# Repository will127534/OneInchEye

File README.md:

# OneInchEye: OpenSource IMX283 Camera Board for Raspberry Pi

### Update on 2024/03/24
This project is also compatiable with RPI5, the quickstart guide has been updated.  

## Introduction
Welcome to the **OneInchEye** project, an open-source camera board designed for Raspberry Pi Compute Module 4 boards using the IMX283 one-inch sensor. This project aims to provide a high-quality, affordable, and accessible camera module for advanced Raspberry Pi projects. The board is designed using KiCad v6, a popular open-source electronics design automation (EDA) software.

OneInchEye captures stunning high-resolution images and videos with improved low-light performance and dynamic range. It's perfect for photography enthusiasts, developers, and makers who want to level up their Raspberry Pi projects with a powerful camera. The board also features a TMP117 temperature sensor for accurate temperature readings.

**Please note that the OneInchEye is not compatible with most Raspberry Pi boards because it requires 22-pin FPC connector with 4-lane MIPI-CSI interface. Ensure compatibility with your specific board before proceeding.**

## Features
* 1-inch IMX283 sensor
* **Open-source hardware and software**
* Integrated TMP117 temperature sensor
* Integrated 6-axis IMU ICM42688-P
* Compatible with Raspberry Pi Compute Module 4 boards with a 22-pin FPC connector and 4-lane MIPI-CSI (same pinout as Raspberry Pi Compute Module 4 IO Board)

## Support
For questions, issues, or suggestions, please open an issue in the [GitHub repository](https://github.com/will127534/OneInchEye/issues)  
Also see [Quick Start Guide](https://github.com/will127534/OneInchEye/wiki/OneInchEye-Quick-Start-Guide)

## MISC stuff  
1. Blog post(?) here: https://will127534.github.io/OneInchEye/
1. I know the decoupling capacitors in sch are a mess.....  
2. IMU is hook up at the 1.8V LDO, but that LDO is controlled by CAM_GPIO (or think as a enable pin for the camera module), so it will function only when the camera is active.
3. IMU's FSYNC is conencted to VSYNC output from the sensor for measurements/frame alignment 
4. Temperature sensor is connected to 3.3V FPC input
5. There is no clock sync function for the CMOS sensor, so the XVS and XHS are output only.  
6. QWIIC is mainly for hooking up to other I2C devices so you don't have to connect yet another cable if you add additional I2C sensor to the board. But it also serves as I2C debug port to hook up external logic analyzer.  
7. This board is actually quite easy to assemble, if you want to build board yourself, you can use JLCPCB to do the PCBA on component side and do the CMOS side with low temperature soldering paste yourself if you can source the CMOS sensor. The JLCPCB BOM and Position list is also provided.
8. Limited quantity on Tindle: https://www.tindie.com/products/will123321/oneincheye/

## License
This project is released under the MIT License.

Thanks to ChatGPT helping me generating most of the Readme, see if you can spot which section I typed.

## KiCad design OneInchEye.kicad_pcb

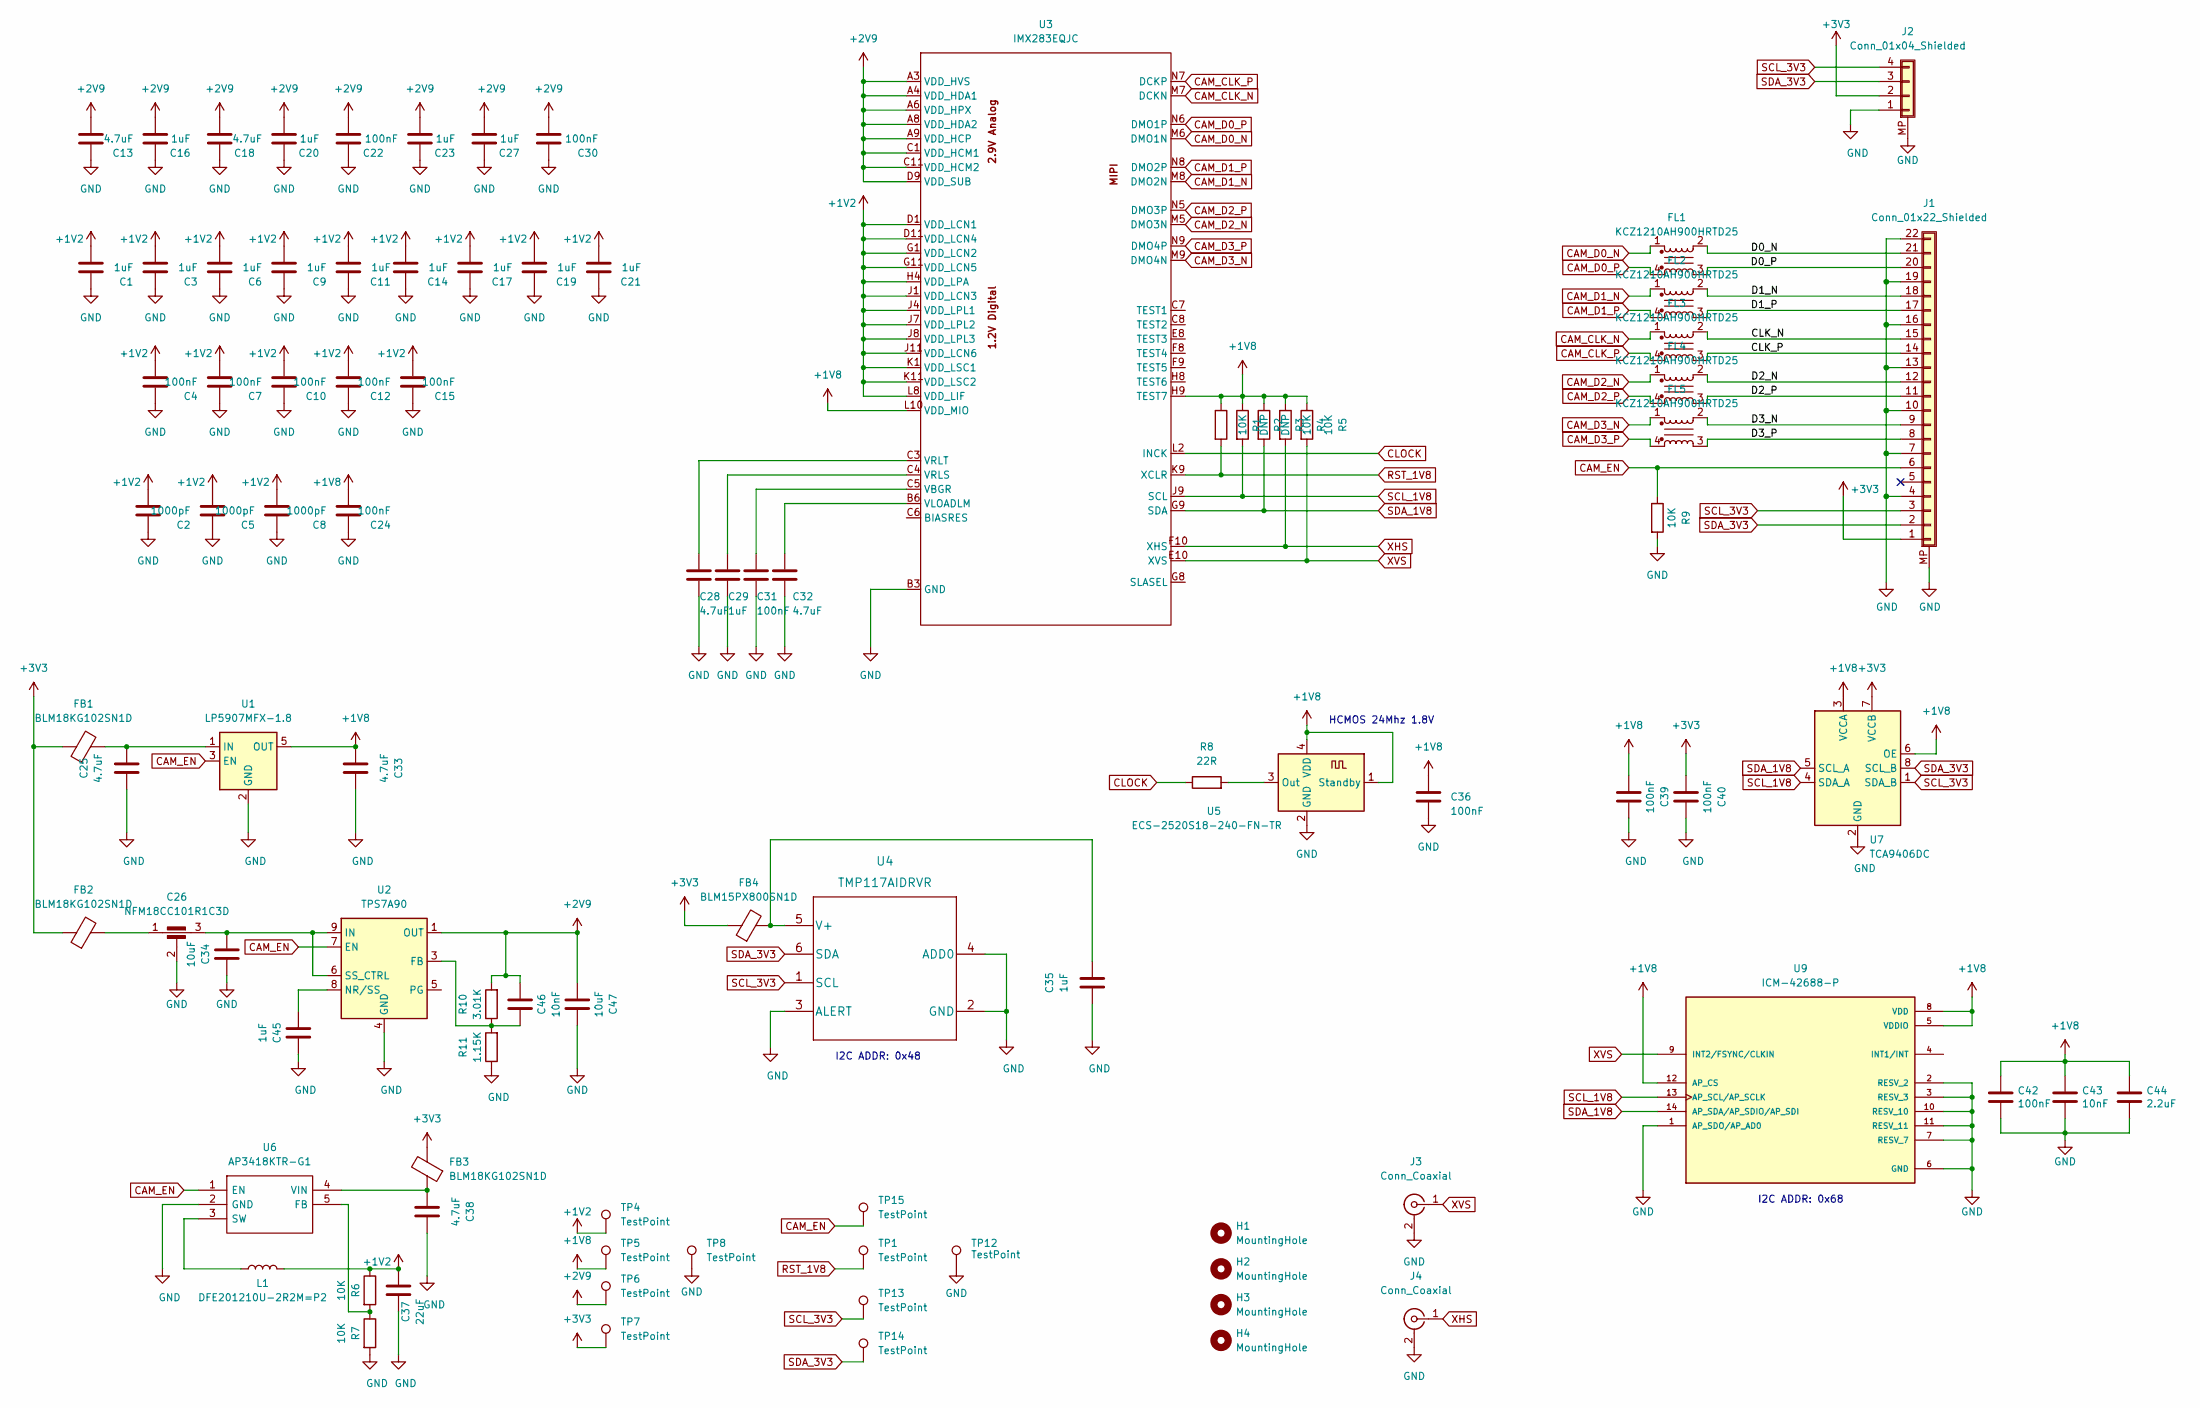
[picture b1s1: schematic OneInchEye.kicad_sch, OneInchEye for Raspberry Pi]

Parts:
C1, C3, C6, C9, C11, C14, C16, C17, C19, C20, C21, C23, C27, C29, C35, C45: 1uF; C_0402_1005Metric
C2, C5, C8: 1000pF; C_0402_1005Metric
C4, C7, C10, C12, C15, C22, C24, C30, C31, C36, C39, C40, C42: 100nF; C_0402_1005Metric
C13, C18, C25, C28, C32, C33, C38: 4.7uF; C_0603_1608Metric
C26: NFM18CC101R1C3D
C34, C47: 10uF; C_0603_1608Metric
C37: 22uF; C_0603_1608Metric
C43, C46: 10nF; C_0402_1005Metric
C44: 2.2uF; C_0402_1005Metric
FB1, FB2, FB3: BLM18KG102SN1D; L_0603_1608Metric
FB4: BLM15PX800SN1D; L_0402_1005Metric
FL1, FL2, FL3, FL4, FL5: KCZ1210AH900HRTD25; DLP11SA350HL2B
H1, H2, H3, H4: MountingHole; MountingHole_2.2mm_M2
J1: Conn_01x22_Shielded; TF3822S05SV830
J2: Conn_01x04_Shielded; JST_SH_BM04B-SRSS-TB_1x04-1MP_P1.00mm_Vertical
J3, J4: Conn_Coaxial; U.FL_Hirose_U.FL-R-SMT-1_Vertical
L1: DFE201210U-2R2M=P2; L_0805_2012Metric
R1, R4, R5, R6, R7, R9: 10K; R_0402_1005Metric
R2, R3: DNP; R_0402_1005Metric
R8: 22R; R_0402_1005Metric
R10: 3.01K; R_0402_1005Metric
R11: 1.15K; R_0402_1005Metric
TP1, TP4, TP5, TP6, TP7, TP8, TP12, TP13, TP14, TP15: TestPoint; TestPoint_Pad_D1.0mm
U1: LP5907MFX-1.8; SOT-23-5
U2: TPS7A90; Texas_S-PDSO-N10_EP1.2x2mm
U3: IMX283EQJC; IMX283
U4: TMP117AIDRVR
U5: ECS-2520S18-240-FN-TR; Oscillator_SMD_Abracon_ASDMB-4Pin_2.5x2.0mm
U6: AP3418KTR-G1; SOT-23-5; Mouser Part Number 621-AP3418KTR-G1
U7: TCA9406DC; TCA9406DCUR
U9: ICM-42688-P; IIM42352; PARTREV 1.2

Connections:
+1V2: C1.2, C2.2, C3.2, C4.2, C5.2, C6.2, C7.2, C8.2, C9.2, C10.2, C11.2, C12.2, C14.2, C15.2, C17.2, C19.2, C21.2, C37.2, L1.2, R6.1, TP4.1, U3.D1 (VDD_LCN1), U3.D11 (VDD_LCN4), U3.G1 (VDD_LCN2), U3.G11 (VDD_LCN5), U3.H4 (VDD_LPA), U3.J1 (VDD_LCN3), U3.J4 (VDD_LPL1), U3.J7 (VDD_LPL2), U3.J8 (VDD_LPL3), U3.J11 (VDD_LCN6), U3.K1 (VDD_LSC1), U3.K11 (VDD_LSC2), U3.L8 (VDD_LIF)
+1V8: C24.2, C33.1, C36.1, C39.1, C42.1, C43.1, C44.1, R1.1, R2.1, R3.1, R4.1, R5.1, TP5.1, U1.5 (OUT), U3.H9 (TEST7), U3.L10 (VDD_MIO), U5.1 (Standby), U5.4 (VDD), U7.3 (VCCA), U7.6 (OE), U9.5 (VDDIO), U9.8 (VDD), U9.12 (AP_CS)
+2V9: C13.2, C16.2, C18.2, C20.2, C22.2, C23.2, C27.2, C30.2, C46.2, C47.1, R10.2, TP6.1, U2.1 (OUT), U2.2 (OUT), U3.A3 (VDD_HVS), U3.A4 (VDD_HDA1), U3.A6 (VDD_HPX), U3.A8 (VDD_HDA2), U3.A9 (VDD_HCP), U3.C1 (VDD_HCM1), U3.C11 (VDD_HCM2), U3.D9 (VDD_SUB)
+3V3: C40.1, FB1.1, FB2.1, FB3.2, FB4.1, J1.1, J2.2, TP7.1, U7.7 (VCCB)
/CLK_N: FL3.2, J1.15
/CLK_P: FL3.3, J1.14
/D0_N: FL1.2, J1.21
/D0_P: FL1.3, J1.20
/D1_N: FL2.2, J1.18
/D1_P: FL2.3, J1.17
/D2_N: FL4.2, J1.12
/D2_P: FL4.3, J1.11
/D3_N: FL5.2, J1.9
/D3_P: FL5.3, J1.8
CAM_CLK_N: FL3.1, U3.M7 (DCKN)
CAM_CLK_P: FL3.4, U3.N7 (DCKP)
CAM_D0_N: FL1.1, U3.M6 (DMO1N)
CAM_D0_P: FL1.4, U3.N6 (DMO1P)
CAM_D1_N: FL2.1, U3.M8 (DMO2N)
CAM_D1_P: FL2.4, U3.N8 (DMO2P)
CAM_D2_N: FL4.1, U3.M5 (DMO3N)
CAM_D2_P: FL4.4, U3.N5 (DMO3P)
CAM_D3_N: FL5.1, U3.M9 (DMO4N)
CAM_D3_P: FL5.4, U3.N9 (DMO4P)
CAM_EN: J1.6, R9.1, TP15.1, U1.3 (EN), U2.7 (EN), U6.1 (EN)
CLOCK: R8.1, U3.L2 (INCK)
GND: C1.1, C2.1, C3.1, C4.1, C5.1, C6.1, C7.1, C8.1, C9.1, C10.1, C11.1, C12.1, C13.1, C14.1, C15.1, C16.1, C17.1, C18.1, C19.1, C20.1, C21.1, C22.1, C23.1, C24.1, C25.1, C26.2, C27.1, C28.2, C29.2, C30.1, C31.2, C32.2, C33.2, C34.2, C35.1, C36.2, C37.1, C38.2, C39.2, C40.2, C42.2, C43.2, C44.2, C45.2, C47.2, J1.4, J1.7, J1.10, J1.13, J1.16, J1.19, J1.22, J1.MP (Shield), J2.1, J2.MP (Shield), J3.2 (Ext), J4.2 (Ext), R7.2, R9.2, R11.1, TP8.1, TP12.1, U1.2 (GND), U2.4 (GND), U2.11 (GND), U3.B3 (GND), U3.B4 (GND2), U3.B5 (GND3), U3.B7 (GND4), U3.B8 (GND5), U3.B9 (GND6), U3.C2 (GND8), U3.C10 (GND7), U3.D2 (GND9), U3.D10 (GND10), U3.G2 (GND11), U3.G10 (GND12), U3.H2 (GND13), U3.H3 (GND14), U3.H10 (GND15), U3.J2 (GND16), U3.J10 (GND17), U3.K2 (GND18), U3.K4 (GND19), U3.K7 (GND20), U3.K8 (GND21), U3.K10 (GND22), U3.L7 (GND23), U3.L9 (GND24), U3.N4 (GND25), U4.2 (GND), U4.3 (ALERT), U4.4 (ADD0), U5.2 (GND), U6.2 (GND), U7.2 (GND), U9.1 (AP_SDO/AP_AD0), U9.2 (RESV_2), U9.3 (RESV_3), U9.6 (GND), U9.7 (RESV_7), U9.10 (RESV_10), U9.11 (RESV_11)
unnamed: C26.1, FB2.2
unnamed: C25.2, FB1.2, U1.1 (IN)
unnamed: C46.1, R10.1, R11.2, U2.3 (FB)
unnamed: C45.1, U2.8 (NR/SS)
unnamed: C26.3, C34.1, U2.6 (SS_CTRL), U2.9 (IN), U2.10 (IN)
unnamed: C31.1, U3.C5 (VBGR)
unnamed: C32.1, U3.B6 (VLOADLM)
unnamed: C29.1, U3.C4 (VRLS)
unnamed: C28.1, U3.C3 (VRLT)
unnamed: C35.2, FB4.2, U4.5 (V+)
unnamed: R8.2, U5.3 (Out)
unnamed: R6.2, R7.1, U6.5 (FB)
unnamed: L1.1, U6.3 (SW)
unnamed: C38.1, FB3.1, U6.4 (VIN)
RST_1V8: R1.2, TP1.1, U3.K9 (XCLR)
SCL_1V8: R2.2, U3.J9 (SCL), U7.4 (SDA_A), U9.13 (AP_SCL/AP_SCLK)
SCL_3V3: J1.3, J2.4, TP13.1, U4.1 (SCL), U7.1 (SDA_B)
SDA_1V8: R3.2, U3.G9 (SDA), U7.5 (SCL_A), U9.14 (AP_SDA/AP_SDIO/AP_SDI)
SDA_3V3: J1.2, J2.3, TP14.1, U4.6 (SDA), U7.8 (SCL_B)
XHS: J4.1 (In), R4.2, U3.F10 (XHS)
XVS: J3.1 (In), R5.2, U3.E10 (XVS), U9.9 (INT2/FSYNC/CLKIN)

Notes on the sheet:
I2C ADDR: 0x48
I2C ADDR: 0x68
HCMOS 24Mhz 1.8V

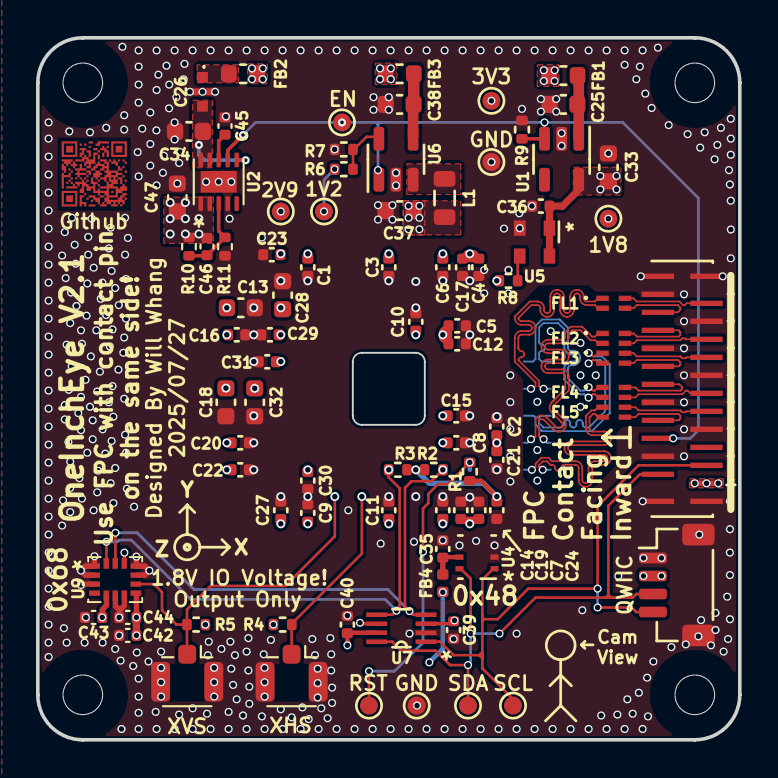
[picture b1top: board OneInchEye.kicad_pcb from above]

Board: 4 copper layers, 39.0 x 39.0 mm, 93 parts (1 on the bottom side), 48 nets.

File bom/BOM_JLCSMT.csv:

Comment,Designator,Footprint,JLCPCB Part #（optional）
100nF,"C7,C36,C22,C15,C24,C12,C10,C31,C30,C4",C_0402_1005Metric,C110251
DLP11SN900HL2L,"FL1,FL4,FL5,FL2,FL3",DLP11SA350HL2B,C90762
22uF,C37,C_0603_1608Metric,C59461
1uF,"C14,C27,C9,C21,C16,C17,C1,C3,C23,C11,C35,C29,C20,C19,C6",C_0402_1005Metric,C115046
1000pF,"C8,C2,C5",C_0402_1005Metric,C343059
10K,"R7,R1,R6,R4,R3,R2,R5",R_0402_1005Metric,C60490
4.7uF,"C34,C38,C26,C18,C32,C28,C13,C33,C25",C_0603_1608Metric,C389010
SI2302,"Q1,Q2",SOT-23,C181087
LP5907MFX-1.8,U1,SOT-23-5,C92498
FH12A-22S-0.5SH(55),J1,Hirose_FH12-22S-0.5SH_1x22-1MP_P0.50mm_Horizontal,C3168813
LP5907MFX-2.9,U2,SOT-23-5,C2877839
QWIIC_CONNECTORJS-1MM,J2,JST_SH_SM04B-SRSS-TB_1x04-1MP_P1.00mm_Horizontal,C160404
BLM18KG102SN1D,"FB2,FB3,FB1",L_0603_1608Metric,C160982
22R,R8,R_0402_1005Metric,C325393
DFE201210U-2R2M=P2,L1,L_0805_2012Metric,C2049745
CO22H4-24.000-WPJDTSN,U5,Oscillator_SMD_Abracon_ASDMB-4Pin_2.5x2.0mm,C2842194
AP3418KTR-G1,U6,SOT-23-5,C500769
TMP117MAIDRVR,U4,TMP117AIDRVR,C2803242

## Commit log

2023-03-20 init v1.3
2023-04-09 Adding correct BOM
2023-04-09 Update SOT-32 NMOS part number
2023-04-10 Adding blog post
2024-10-06 Adding IMU and update board outline to 39mm square
2026-01-02 V2.1
